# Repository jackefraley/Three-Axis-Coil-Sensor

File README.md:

# Coil Array Block Project
This folder contains a KiCad hardware design for a magnetic-field sensing block.

## Project
### CoilArrayBlock
Analog sensing block containing only:

- Current transformer front end: CWS CT-0705-HA (CT-0705-HA)
- Instrumentation amplifier stage: AD8422 (AD8422ARMZ)
- Input/output connector stage: JST B2B-XH-A (B2B-XH-A)

## Interfaces
- `Env_array_magfield`: magnetic field input to the sensing front end
- `Pwr_array_dcpwr`: `VCC` supply input
- `Pwr_array_vref`: `Vref` reference input
- `Array_sigproc_asig`: `Vout` analog signal output

## Repository Notes
This project includes KiCad source files (`.kicad_sch`, `.kicad_pcb`, `.kicad_pro`) and generated Gerbers.
Supporting documentation is included in `docs/`.
KiCad backup archives and local transient files are excluded via `.gitignore`.

## PCB Image

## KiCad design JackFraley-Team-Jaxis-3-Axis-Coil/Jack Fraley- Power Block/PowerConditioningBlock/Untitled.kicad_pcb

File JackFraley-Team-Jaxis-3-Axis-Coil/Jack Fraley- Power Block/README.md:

# Power Conditioning Block Projects

This folder contains two KiCad hardware designs split by function.

## Projects

### `PowerBlock`
Power supply block containing only:

- 5V buck converter: `LM62460Q1` (LM62460QRPHRQ1)
- 3.3V linear regulator: `TPS7A94` (PTPS7A9401DSCR)
- Comparator stage: `TLV6710` (TLV6710DDCT)

### `PowerConditioningBlock`
Precision conditioning/reference block containing:

- `ADR4525` precision voltage reference (ADR4525ARZ)
- `TPS7A94` low-noise LDO (PTPS7A9401DSCR)
- `OPA2211` precision op-amp (OPA2211AIDDAR)

## Repository Notes

- Each project includes KiCad source files (`.kicad_sch`, `.kicad_pcb`, `.kicad_pro`) and generated Gerbers.
- KiCad backup archives and local transient files are excluded via `.gitignore`.

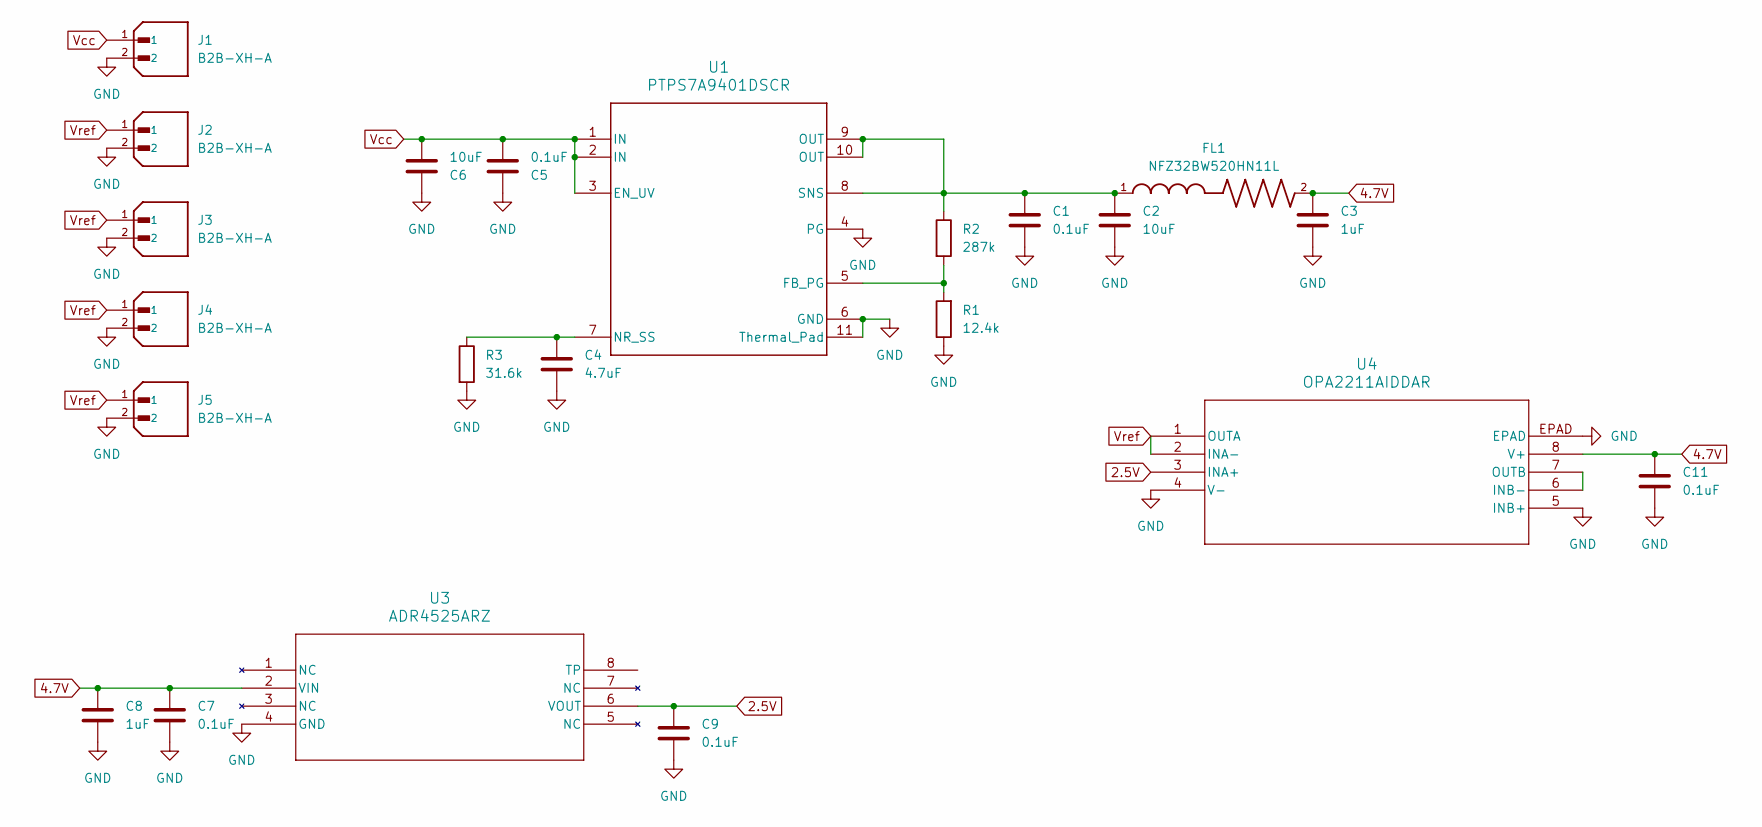
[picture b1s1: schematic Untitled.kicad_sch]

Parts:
C1, C5, C7, C9, C11: 0.1uF; C_0603_1608Metric
C2, C6: 10uF; C_0603_1608Metric
C3, C8: 1uF; C_0603_1608Metric
C4: 4.7uF; C_0603_1608Metric
FL1: NFZ32BW520HN11L; FIL_NFZ32BW520HN11L; DigiKey_Part_Number 490-NFZ32BW520HN11LCT-ND
J1, J2, J3, J4, J5: B2B-XH-A; JST_B2P-VH_LF__SN_; PARTREV N/A
R1: 12.4k; R_0603_1608Metric
R2: 287k; R_0603_1608Metric
R3: 31.6k; R_0603_1608Metric
U1: PTPS7A9401DSCR; DSC0010J-MFG
U3: ADR4525ARZ; R_8_ADI
U4: OPA2211AIDDAR; DDA8_3X2P49

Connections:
2.5V: C9.1, U3.6 (VOUT), U4.3 (INA+)
4.7V: C3.1, C7.1, C8.1, C11.1, FL1.2, U3.2 (VIN), U4.8 (V+)
GND: C1.2, C2.2, C3.2, C4.2, C5.1, C6.1, C7.2, C8.2, C9.2, C11.2, J1.2, J2.2, J3.2, J4.2, J5.2, R1.1, R3.2, U1.4 (PG), U1.6 (GND), U1.11 (Thermal_Pad), U1.12, U1.13, U1.14, U1.15, U3.4 (GND), U4.4 (V-), U4.5 (INB+), U4.EPAD
unnamed: R1.2, R2.2, U1.5 (FB_PG)
unnamed: C4.1, R3.1, U1.7 (NR_SS)
unnamed: C1.1, C2.1, FL1.1, R2.1, U1.8 (SNS), U1.9 (OUT), U1.10 (OUT)
unnamed: U4.6 (INB-), U4.7 (OUTB)
Vcc: C5.2, C6.2, J1.1, U1.1 (IN), U1.2 (IN), U1.3 (EN_UV)
Vref: J2.1, J3.1, J4.1, J5.1, U4.1 (OUTA), U4.2 (INA-)

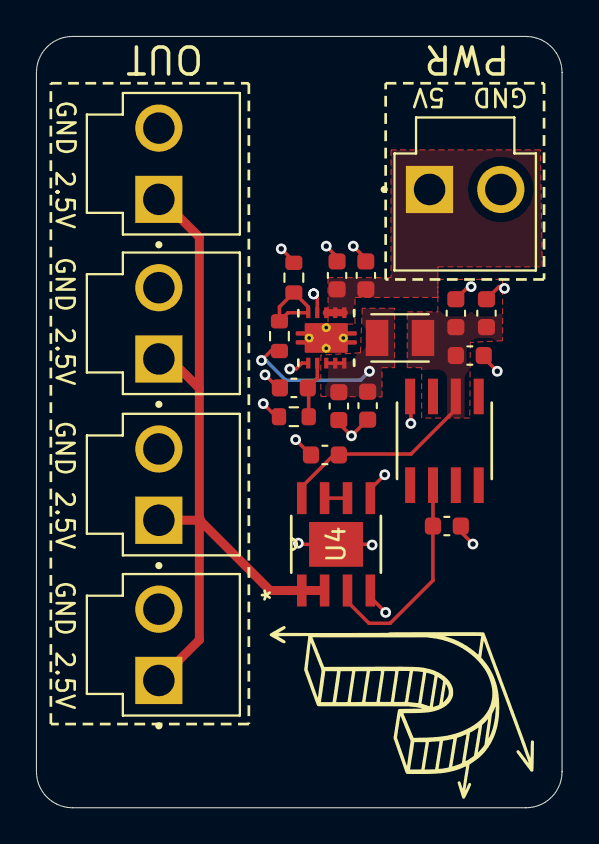
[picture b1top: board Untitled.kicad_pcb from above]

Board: 2 copper layers, 29.2 x 42.9 mm, 22 parts (0 on the bottom side), 9 nets.

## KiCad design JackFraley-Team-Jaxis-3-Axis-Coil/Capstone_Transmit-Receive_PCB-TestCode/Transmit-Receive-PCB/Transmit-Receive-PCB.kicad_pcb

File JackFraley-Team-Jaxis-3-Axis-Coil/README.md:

# Team-Jaxis-3-Axis-Coil
Documentation, resources, code, schematics, pcb layouts, and all related materials for the 3-Axis Coil ECE project at Oregon State University.

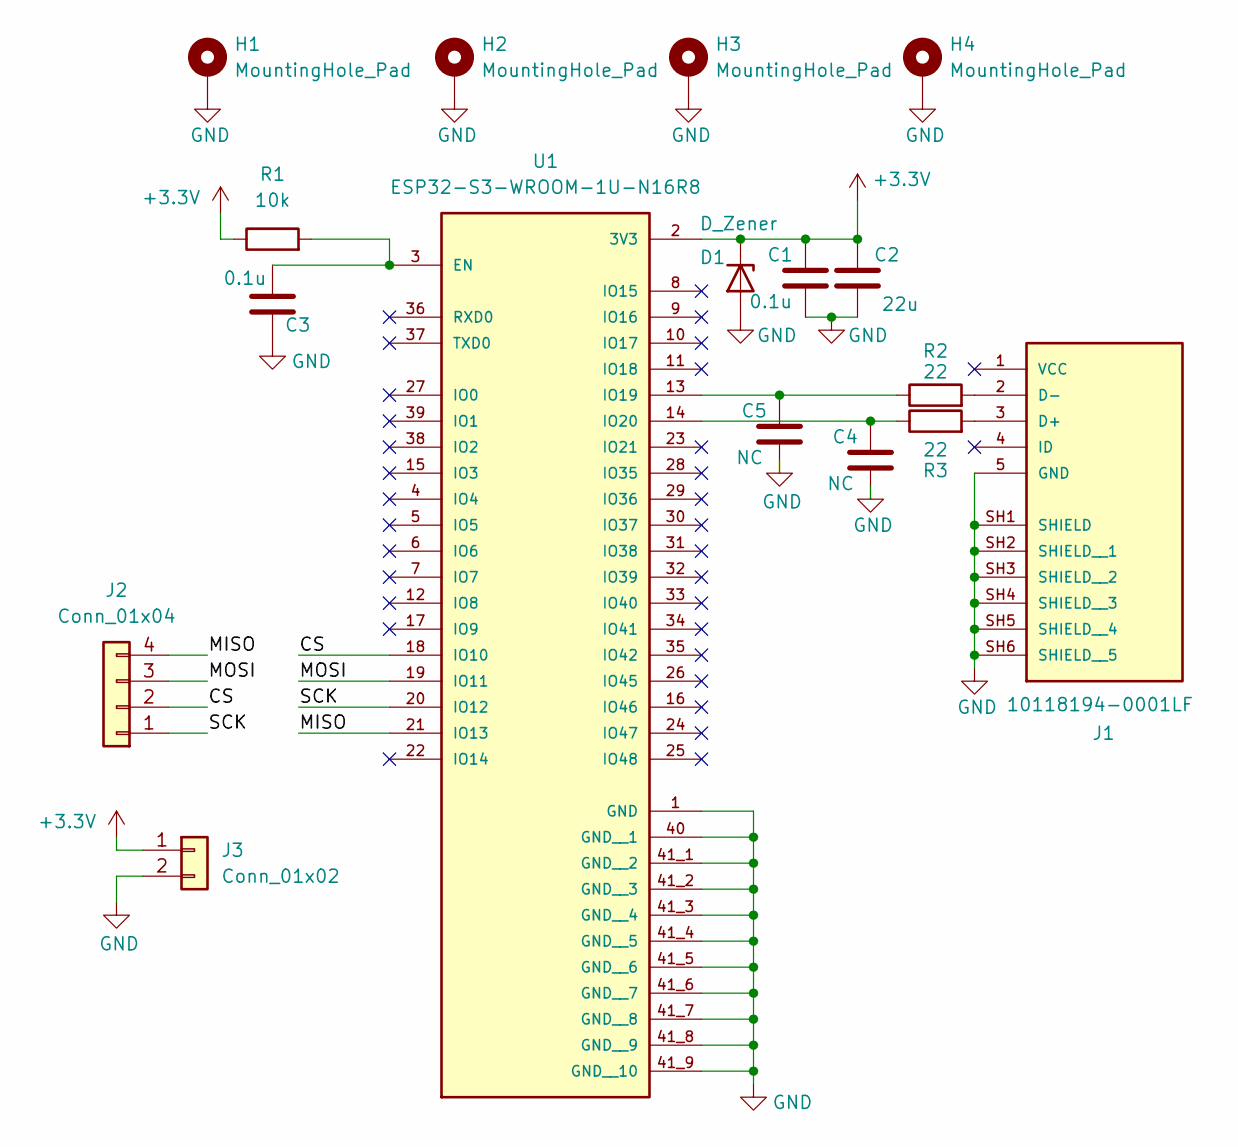
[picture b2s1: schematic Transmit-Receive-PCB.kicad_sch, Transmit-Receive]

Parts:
C1, C3: 0.1u; C_0805_2012Metric_Pad1.18x1.45mm_HandSolder
C2: 22u; C_0805_2012Metric_Pad1.18x1.45mm_HandSolder
C4, C5: NC; C_0805_2012Metric_Pad1.18x1.45mm_HandSolder
D1: D_Zener; SOD123_DIO
H1, H2, H3, H4: MountingHole_Pad; MountingHole_2.2mm_M2_Pad
J1: 10118194-0001LF; AMPHENOL_10118194-0001LF; PARTREV D
J2: Conn_01x04; JST_XH_B4B-XH-AM_1x04_P2.50mm_Vertical
J3: Conn_01x02; JST_XH_B2B-XH-AM_1x02_P2.50mm_Vertical
R1: 10k; R_0805_2012Metric_Pad1.20x1.40mm_HandSolder
R2, R3: 22; R_0805_2012Metric_Pad1.20x1.40mm_HandSolder
U1: ESP32-S3-WROOM-1U-N16R8; XCVR_ESP32-S3-WROOM-1U-N16R8; PARTREV v1.1

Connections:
+3.3V: C1.2, C2.2, D1.1 (K), J3.1, R1.1, U1.2 (3V3)
/CS: J2.2, U1.18 (IO10)
/MISO: J2.4, U1.21 (IO13)
/MOSI: J2.3, U1.19 (IO11)
/SCK: J2.1, U1.20 (IO12)
GND: C1.1, C2.1, C3.2, C4.1, C5.1, D1.2 (A), H1.1, H2.1, H3.1, H4.1, J1.5 (GND), J1.SH1 (SHIELD), J1.SH2 (SHIELD__1), J1.SH3 (SHIELD__2), J1.SH4 (SHIELD__3), J1.SH5 (SHIELD__4), J1.SH6 (SHIELD__5), J3.2, U1.1 (GND), U1.40 (GND__1), U1.41_1 (GND__2), U1.41_2 (GND__3), U1.41_3 (GND__4), U1.41_4 (GND__5), U1.41_5 (GND__6), U1.41_6 (GND__7), U1.41_7 (GND__8), U1.41_8 (GND__9), U1.41_9 (GND__10), U1.41_10, U1.41_11, U1.41_12, U1.41_13, U1.41_14, U1.41_15, U1.41_16, U1.41_17, U1.41_18, U1.41_19, U1.41_20, U1.41_21
unnamed: J1.3 (D+), R3.2
unnamed: J1.2 (D-), R2.2
unnamed: C3.1, R1.2, U1.3 (EN)
unnamed: C5.2, R2.1, U1.13 (IO19)
unnamed: C4.2, R3.1, U1.14 (IO20)

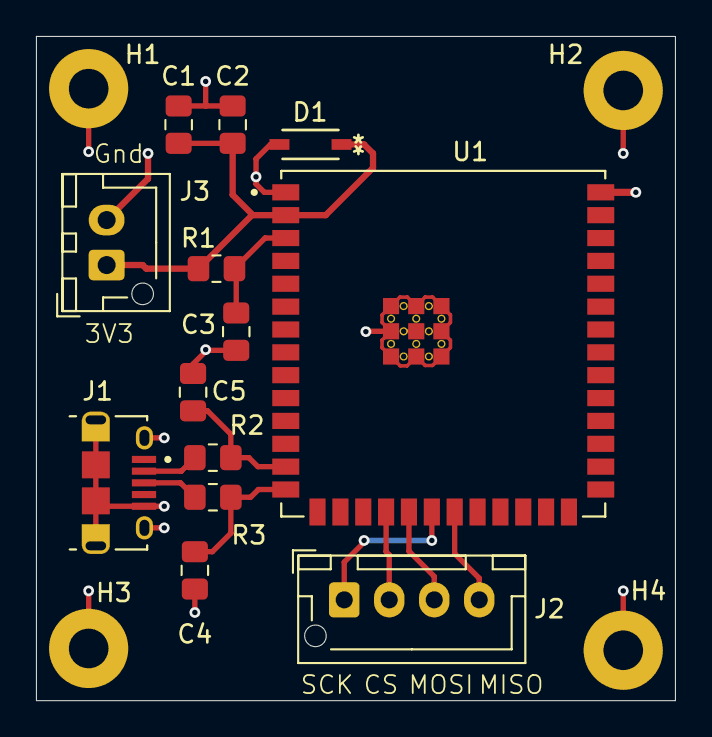
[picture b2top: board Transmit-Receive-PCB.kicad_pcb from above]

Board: 4 copper layers, 35.5 x 36.9 mm, 17 parts (0 on the bottom side), 11 nets.

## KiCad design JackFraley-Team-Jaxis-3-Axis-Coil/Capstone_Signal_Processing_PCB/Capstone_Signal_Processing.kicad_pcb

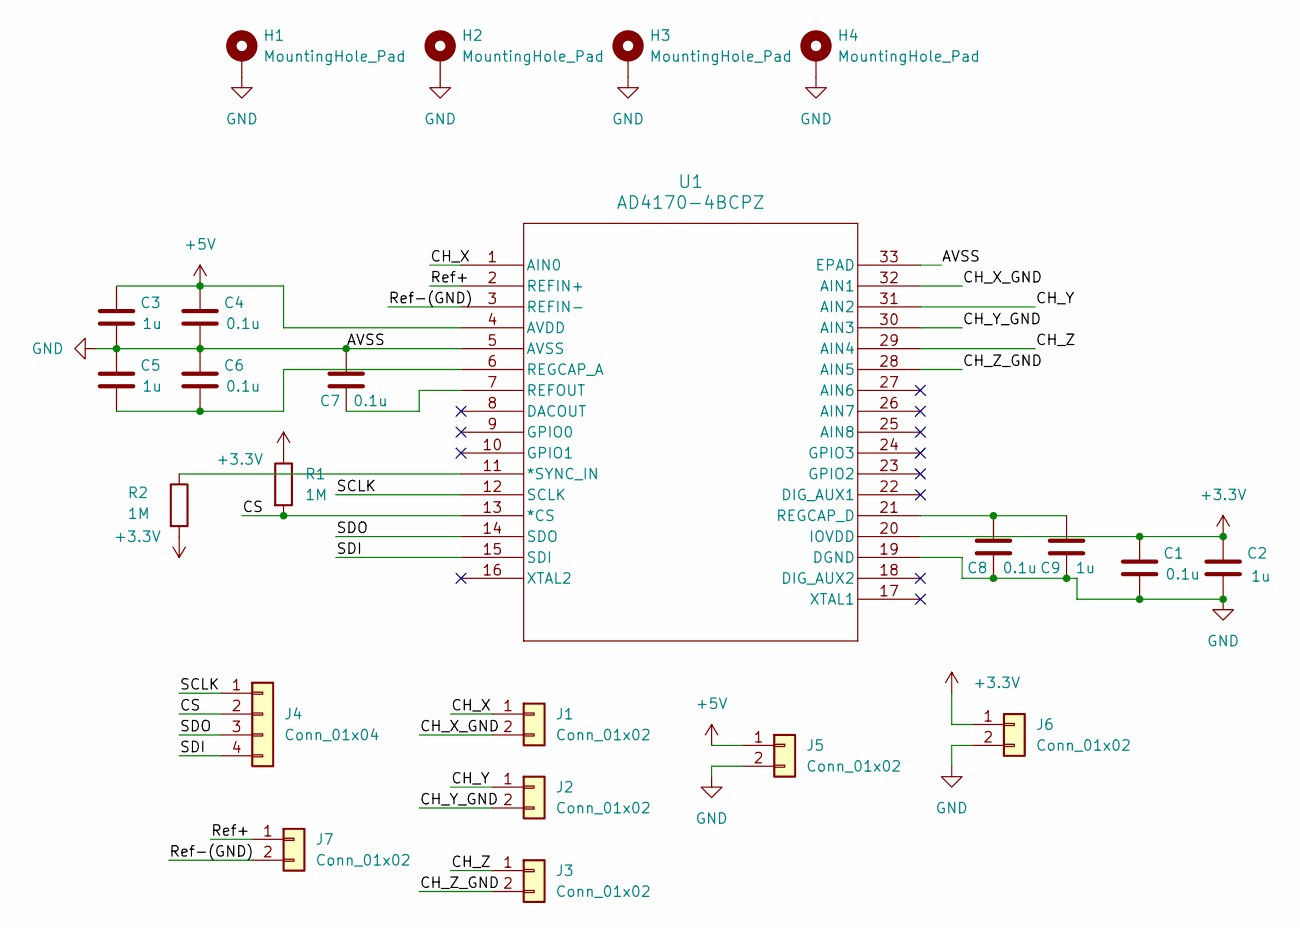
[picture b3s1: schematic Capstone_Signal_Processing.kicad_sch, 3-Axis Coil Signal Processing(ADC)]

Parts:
C1, C4, C6, C7, C8: 0.1u; C_0805_2012Metric_Pad1.18x1.45mm_HandSolder
C2, C3, C5, C9: 1u; C_0805_2012Metric_Pad1.18x1.45mm_HandSolder
H1, H2, H3, H4: MountingHole_Pad; MountingHole_2.2mm_M2_Pad
J1, J2, J3, J5, J6, J7: Conn_01x02; JST_XH_B2B-XH-AM_1x02_P2.50mm_Vertical
J4: Conn_01x04; JST_XH_B4B-XH-AM_1x04_P2.50mm_Vertical
R1, R2: 1M; R_0805_2012Metric_Pad1.20x1.40mm_HandSolder
U1: AD4170-4BCPZ; CP-32-34_ADI

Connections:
+3.3V: C1.1, C2.1, J6.1, R1.1, R2.2, U1.20 (IOVDD)
+5V: C3.1, C4.1, J5.1, U1.4 (AVDD)
/CH_X: J1.1, U1.1 (AIN0)
/CH_X_GND: J1.2, U1.32 (AIN1)
/CH_Y: J2.1, U1.31 (AIN2)
/CH_Y_GND: J2.2, U1.30 (AIN3)
/CH_Z: J3.1, U1.29 (AIN4)
/CH_Z_GND: J3.2, U1.28 (AIN5)
/CS: J4.2, R1.2, U1.13 (*CS)
/Ref+: J7.1, U1.2 (REFIN+)
/Ref-(GND): J7.2, U1.3 (REFIN-)
/SCLK: J4.1, U1.12 (SCLK)
/SDI: J4.4, U1.15 (SDI)
/SDO: J4.3, U1.14 (SDO)
GND: C1.2, C2.2, C3.2, C4.2, C5.1, C6.1, C7.1, C8.2, C9.2, H1.1, H2.1, H3.1, H4.1, J5.2, J6.2, U1.5 (AVSS), U1.19 (DGND), U1.33 (EPAD)
unnamed: R2.1, U1.11 (*SYNC_IN)
unnamed: C7.2, U1.7 (REFOUT)
unnamed: C5.2, C6.2, U1.6 (REGCAP_A)
unnamed: C8.1, C9.1, U1.21 (REGCAP_D)

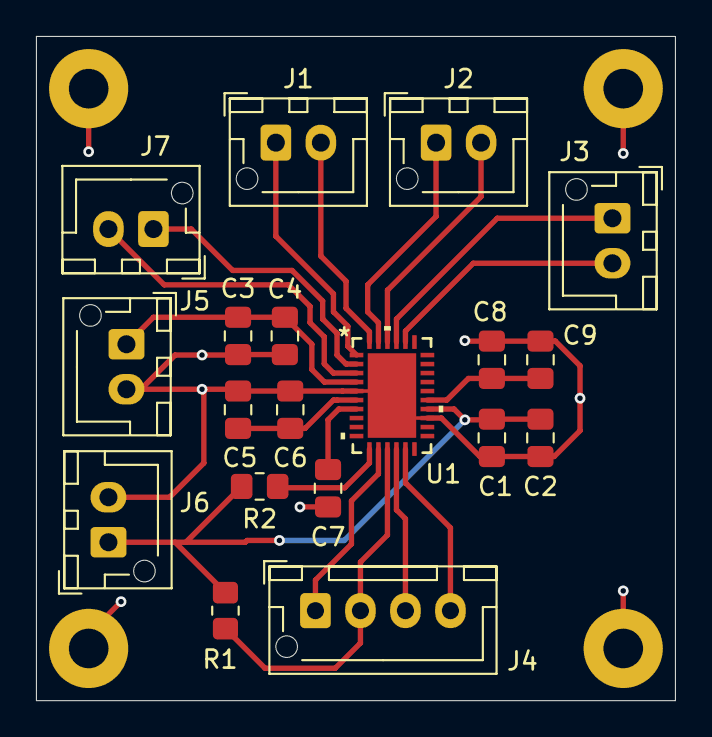
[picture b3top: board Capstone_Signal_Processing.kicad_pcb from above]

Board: 4 copper layers, 35.5 x 36.9 mm, 23 parts (0 on the bottom side), 19 nets.

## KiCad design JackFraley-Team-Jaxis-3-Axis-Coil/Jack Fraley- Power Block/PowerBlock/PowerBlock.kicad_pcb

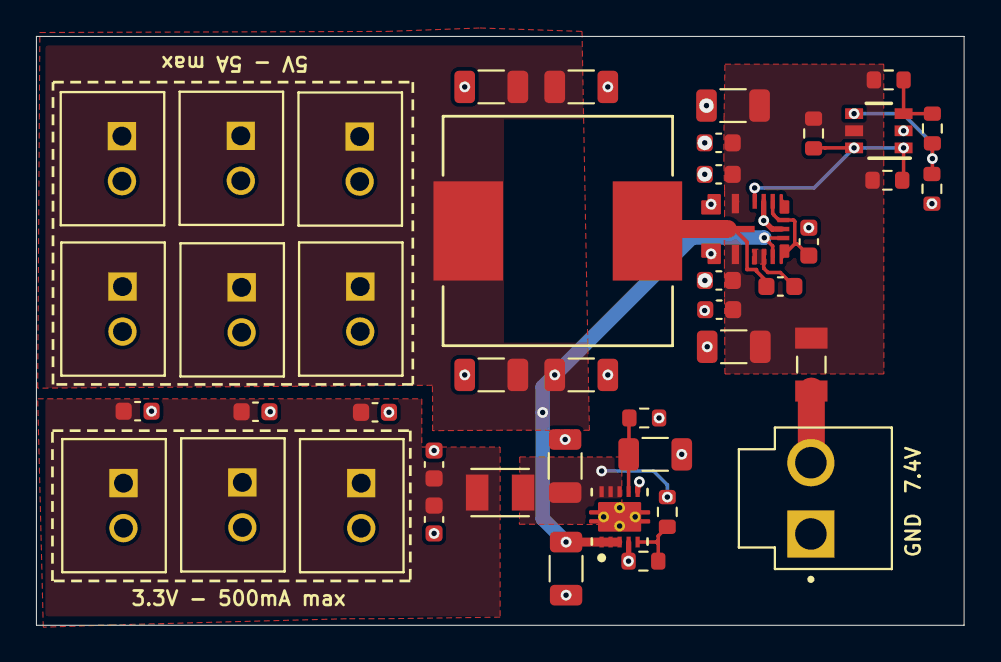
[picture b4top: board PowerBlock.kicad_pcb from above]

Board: 2 copper layers, 51.5 x 32.7 mm, 44 parts (0 on the bottom side), 14 nets.

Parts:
C1: 1uF; C_0603_1608Metric
C2, C3, C4, C5: 0.1uF; C_0603_1608Metric
CBOOT1: 0.1uF; C_0603_1608Metric
CHF1A1, CHF1B1, CHF2A1, CHF2B1: 0.47uF; C_0603_1608Metric
CIN1, CIN2, CIN4: 10uF; C_1206_3216Metric
CNRSS1: 4.7uF; C_1206_3216Metric
COUT4: 10uF; C_1206_3216Metric
COUT51, COUT52, COUT53, COUT54: 22uF; C_1206_3216Metric
CVCC1: 1uF; C_0603_1608Metric
F1: 0685T7000-01; FUSC3215X83N
FL1: NFZ32BW520HN11L; FIL_NFZ32BW520HN11L
J1: B2P-VH_LF__SN_; JST_B2P-VH_LF__SN_
J2, J3, J4, J5, J6, J7, J8, J9, J10: B2B-XH-A; JST_B2B-XH-A
L1: 4.7uH; DR125
R1: 649k; R_0603_1608Metric
R2: 12.8k; R_0603_1608Metric
R3: 31.1k; R_0603_1608Metric
R4, R5: 100k; R_0603_1608Metric
RFB_PGB1: 100k; R_0603_1608Metric
RFB_PGT1: 1.47M; R_0603_1608Metric
RNRSS1: 22.1k; R_0603_1608Metric
U1: LM62460QRPHRQ1; RPH0016A
U2: TLV6710DDCT; DDC0006A_N
U5: PTPS7A9401DSCR; DSC0010J-MFG

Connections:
GND: C1.2, C2.1, C3.1, C4.2, C5.2, CHF1A1.2, CHF1B1.2, CHF2A1.1, CHF2B1.1, CIN1.1, CIN2.1, CIN4.2, CNRSS1.2, COUT4.2, COUT51.2, COUT52.2, COUT53.2, COUT54.2, CVCC1.2, J1.1, J2.2, J3.2, J4.2, J5.2, J6.2, J7.2, J8.2, J9.2, J10.2, R3.1, RFB_PGB1.1, RNRSS1.2, U1.1 (PGND), U1.8 (AGND), U1.12 (SYNC_MODE), U1.15 (PGND), U2.2 (GND), U5.4 (PG), U5.6 (GND), U5.11 (Thermal_Pad)
unnamed: C1.1, C2.2, C3.2, C4.1, C5.1, FL1.2, J2.1, J3.1, J4.1
unnamed: F1.1, J1.2
unnamed: CIN4.1, COUT51.1, COUT52.1, COUT53.1, COUT54.1, J5.1, J6.1, J7.1, J8.1, J9.1, J10.1, L1.2, U1.5 (BIAS), U1.7 (FB), U5.1 (IN), U5.2 (IN), U5.3 (EN_UV)
unnamed: CBOOT1.2, U1.3 (RBOOT), U1.4 (CBOOT)
unnamed: R4.2, R5.1, U1.13 (EN), U2.1 (OUTA), U2.6 (OUTB)
unnamed: CVCC1.1, U1.6 (VCC), U1.9 (RT), U1.11 (SpSp)
unnamed: CBOOT1.1, L1.1, U1.16 (SW)
unnamed: R1.1, R2.1, U2.3 (INA+)
unnamed: R2.2, R3.2, U2.4 (INB-)
unnamed: CHF1A1.1, CHF1B1.1, CHF2A1.2, CHF2B1.2, CIN1.2, CIN2.2, F1.2, R1.2, R4.1, R5.2, U1.2 (VIN), U1.14 (VIN), U2.5 (VDD)
unnamed: RFB_PGB1.2, RFB_PGT1.2, U5.5 (FB_PG)
unnamed: CNRSS1.1, RNRSS1.1, U5.7 (NR_SS)
unnamed: COUT4.1, FL1.1, RFB_PGT1.1, U5.8 (SNS), U5.9 (OUT), U5.10 (OUT)

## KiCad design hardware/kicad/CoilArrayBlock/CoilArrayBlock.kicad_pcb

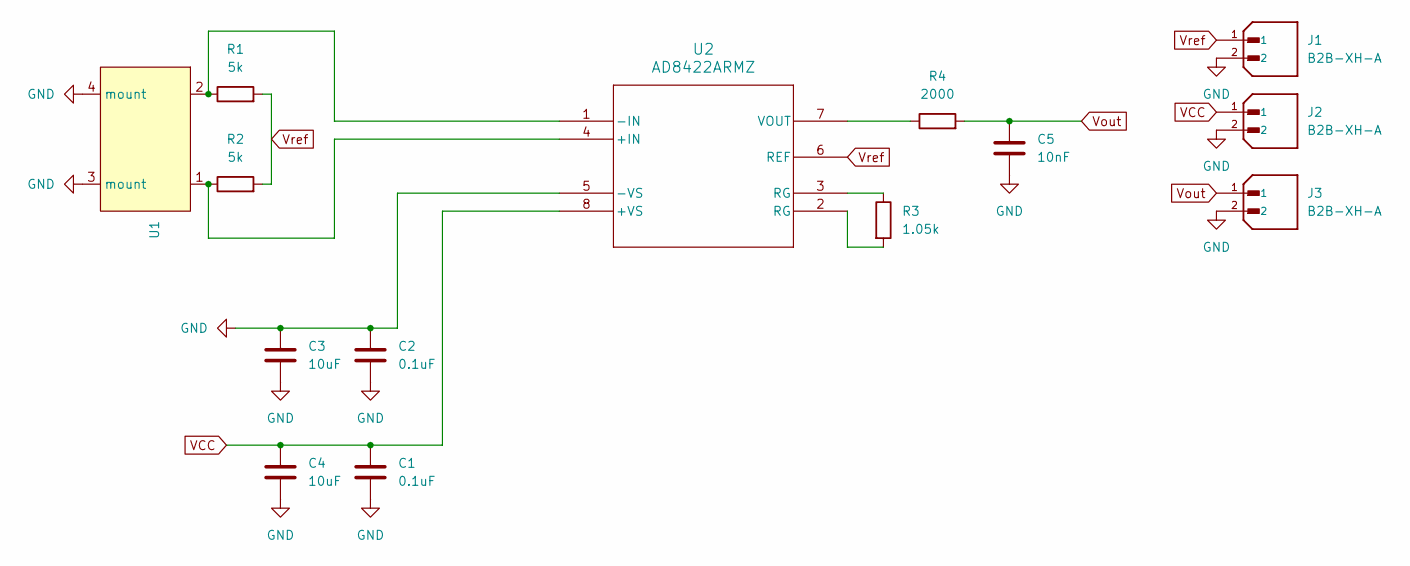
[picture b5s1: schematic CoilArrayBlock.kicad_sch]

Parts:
C1, C2: 0.1uF; C_0603_1608Metric
C3, C4: 10uF; C_0603_1608Metric
C5: 10nF; C_0603_1608Metric
J1, J2, J3: B2B-XH-A; JST_B2B-XH-A; PARTREV N/A
R1, R2: 5k; C_0603_1608Metric
R3: 1.05k; C_0603_1608Metric
R4: 2000; C_0603_1608Metric
U1: CT-0705-HA
U2: AD8422ARMZ; RM_8_ADI

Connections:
GND: C1.1, C2.1, C2.2, C3.1, C3.2, C4.2, C5.2, J1.2, J2.2, J3.2, U1.3 (mount), U1.4 (mount), U2.5 (-VS)
unnamed: R3.1, U2.3 (RG)
unnamed: R3.2, U2.2 (RG)
unnamed: R2.1, U1.1, U2.4 (+IN)
unnamed: R1.1, U1.2, U2.1 (-IN)
unnamed: R4.1, U2.7 (VOUT)
VCC: C1.2, C4.1, J2.1, U2.8 (+VS)
Vout: C5.1, J3.1, R4.2
Vref: J1.1, R1.2, R2.2, U2.6 (REF)

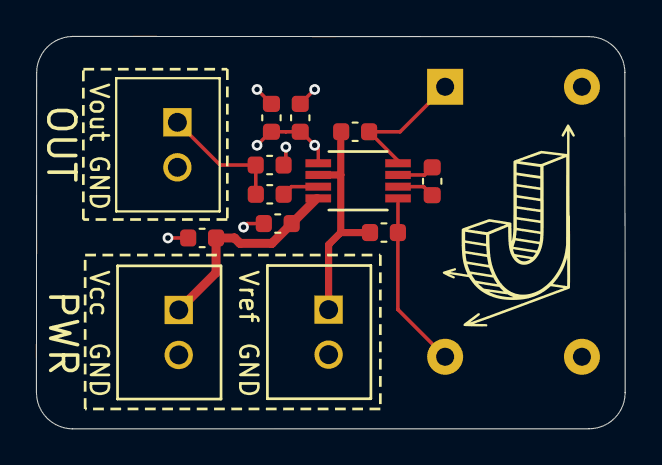
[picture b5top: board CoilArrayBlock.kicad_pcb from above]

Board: 2 copper layers, 32.7 x 21.8 mm, 14 parts (1 on the bottom side), 9 nets.

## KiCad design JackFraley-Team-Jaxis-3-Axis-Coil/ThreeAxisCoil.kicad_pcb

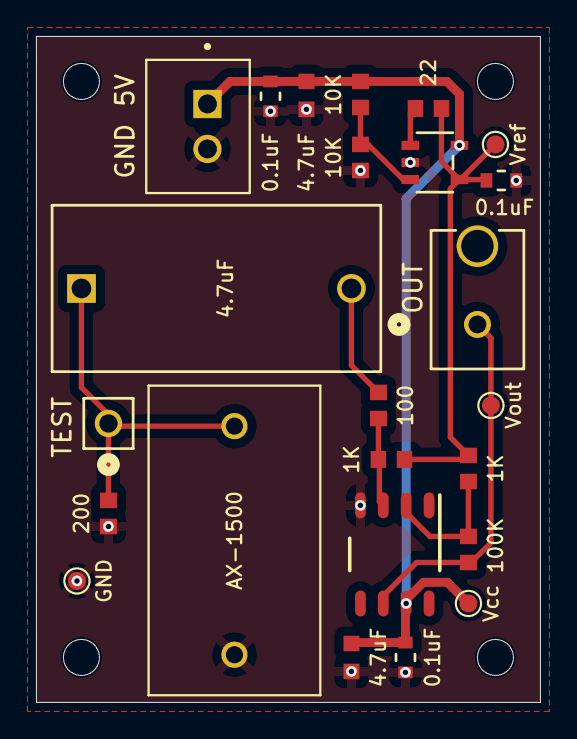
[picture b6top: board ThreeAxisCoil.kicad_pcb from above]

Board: 2 copper layers, 28.0 x 37.0 mm, 24 parts (0 on the bottom side), 10 nets.

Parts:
C1: 4.7uF; CAP_B32522_09.0X17.5X18.0_TDK
C2, C4, C6: 0.1uF; CAP_CL10_SAM
C3, C5: 4.7uF; CAP_0603_CL10A_1P6XP8_SAM
GND: TestPoint_Pad_D1.0mm
J1: B2B-XH-A; JST_B2B-XH-A
J2: B1B-XH-AMLFSNP; CONN_B1B-XH-AMLFSNP_JST
J3: PH1-01-UA; CONN_PH1-01-UA_ADM
R1: 200; RES_TNPW0603_VIS
R2, R3: 10K; RES_TNPW0603_VIS
R4, R6: 1K; RES_TNPW0603_VIS
R5: 100; RES_TNPW0603_VIS
R7: 100K; RES_TNPW0603_VIS
R8: 22; RES_TNPW0603_VIS
T1: AX-1500; INDRR1270W55L1720T953H2040
U1: OPA1611AIDR; D0008A_N
U2: OPA187IDBVT; DBV5_TEX
Vcc: TestPoint_Pad_D1.0mm
Vout: TestPoint_Pad_D1.0mm
Vref: TestPoint_Pad_D1.0mm

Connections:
GND: C2.2, C3.2, C4.2, C5.2, C6.2, GND.1, J1.2, R1.1, R3.1, T1.3, U1.4 (V-), U2.2 (V-)
In-: R6.1, R7.2, U1.2 (IN-)
unnamed: C1.1, J3.1, R1.2, T1.1
unnamed: C1.2, R5.1
unnamed: R4.2, R5.2, U1.3 (IN+)
unnamed: J2.1, R7.1, U1.6 (OUT), Vout.1
unnamed: R8.2, U2.1 (OUT)
V2.5: R2.1, R3.2, U2.3 ('+IN)
VCC: C2.1, C3.1, C4.1, C5.1, J1.1, R2.2, U1.7 (V+), U2.5 (V+), Vcc.1
Vref: C6.1, R4.1, R6.2, R8.1, U2.4 ('-IN), Vref.1

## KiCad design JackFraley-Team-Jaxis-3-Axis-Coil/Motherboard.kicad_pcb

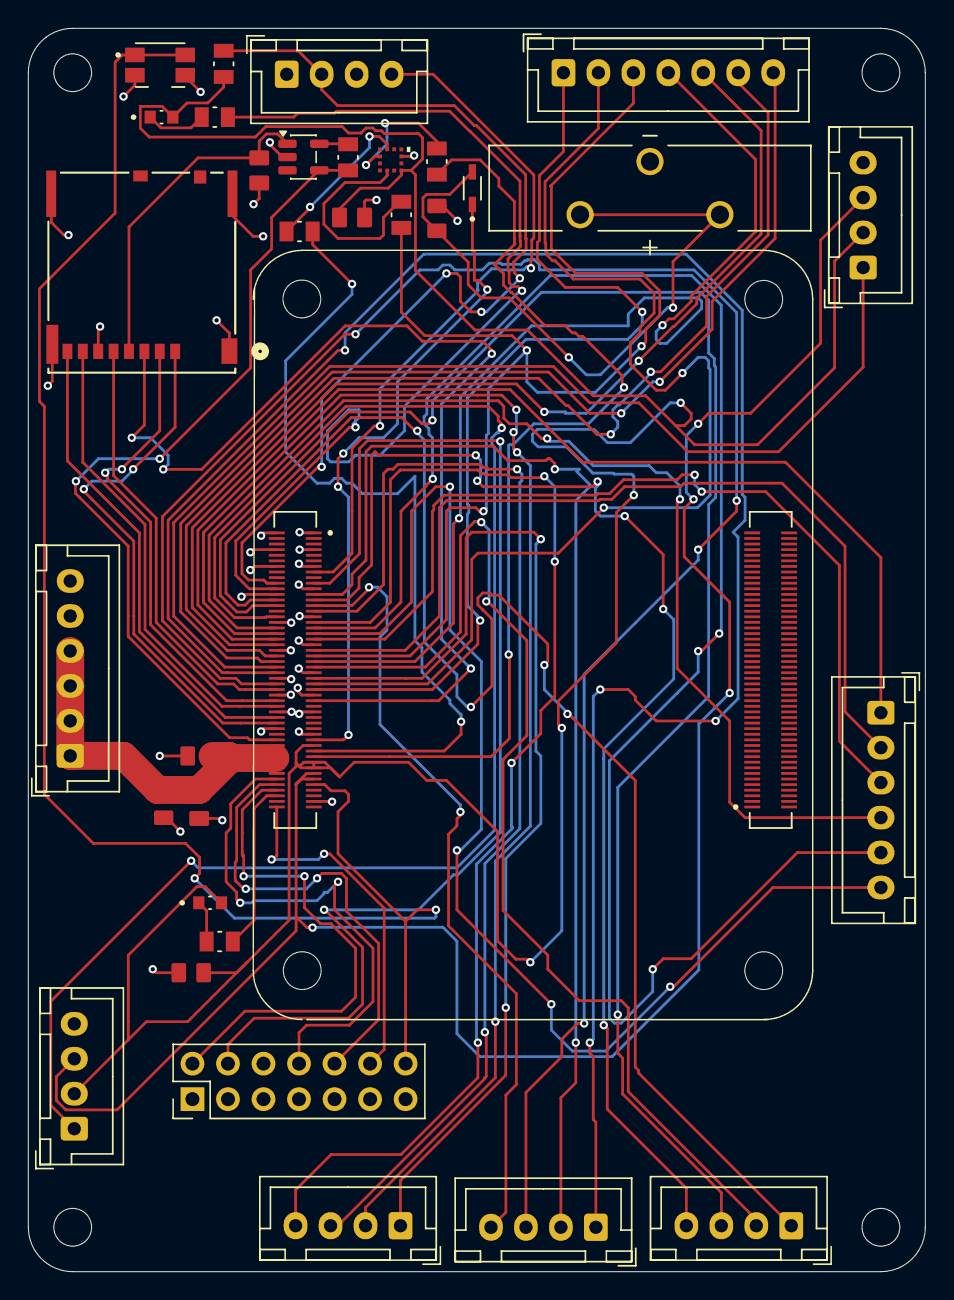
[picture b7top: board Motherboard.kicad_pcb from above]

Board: 2 copper layers, 64.1 x 88.9 mm, 42 parts (0 on the bottom side), 59 nets.

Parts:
BT1: 1074; BAT_1074
C1: 10u; CAPC2012X140N
C2: 4.7u; CAPC2012X140N
C3: 1uF; CAPC2012X135N
C6, C12, C13: 0.1uF; CAPC2012X95N
C7: 10uF; CAPC2012X140N
D2: ZMV829BTA; SOD2512X116N
D4, D5: LTST-C190KRKT; LEDC1608X35N
H1, H2, H3, H4, H5, H6, H7, H8: MountingHole; MountingHole_2.7mm_M2.5
J1, J8: Conn_01x06_Socket; JST_XH_B6B-XH-A_1x06_P2.50mm_Vertical
J2, J3, J4, J5, J6, J10: Conn_01x04_Socket; JST_XH_B4B-XH-A_1x04_P2.50mm_Vertical
J7: Conn_01x07_Socket; JST_XH_B7B-XH-A_1x07_P2.50mm_Vertical
J9: Conn_02x07_Odd_Even; PinHeader_2x07_P2.54mm_Vertical
J12, J13: 10164227-1001A1RLF; AMPHENOL_10164227-1001A1RLF
J14: 5033981892; CONN_503398-1892_MOL
R1, R5: 10k; RESC2012X65N
R2, R6, R7: 2.7k; RESC2012X65N
R3, R4: 1k; RESC2012X65N
S1: EVQ-P7A01P; SW_EVQ-P7A01P
U1: RT9742GGJ5; SOT-23-5
U2: MXC6655XA; MXC6655XA_MEM

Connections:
1.8VO: J5.3, J6.3, J12.87, J12.89
3.3VI: R5.1, U1.5 (IN)
3.3VO: C2.1, C13.2, D4.A, D5.A, J5.2, J6.2, J12.77, J12.83, J12.85, R1.2, U2.7 (VDD)
5VI: C6.1, C7.1, C12.1, J8.1, J8.2, J8.3, J8.4, J12.78, J12.80, J12.82, J12.84, J12.86, J12.88
BT_nDisable: J9.10, J12.92
EEPROM_nWP: J9.4, J12.19
FANPWM: J10.2, J12.20, R1.1
GND: BT1.N, C1.2, C2.2, C3.2, C6.2, C7.2, C12.2, C13.1, J5.4, J6.4, J8.5, J8.6, J9.1, J9.3, J9.5, J9.7, J9.9, J9.11, J9.13, J10.3, J12.1, J12.2, J12.7, J12.8, J12.13, J12.14, J12.21, J12.24, J12.31, J12.34, J12.41, J12.44, J12.51, J12.54, J12.59, J12.60, J12.65, J12.66, J12.72, J12.73, J12.97, J14.6 (VSS), J14.11, J14.12, J14.13, J14.14, S1.2_1, S1.2_2, U1.2 (GND), U2.9 (GND)
GPIO0: J1.5, J12.35
GPIO1: J1.4, J12.36
GPIO2: J7.1, J12.57
GPIO3: J7.2, J12.55
GPIO4: J3.1, J12.53
GPIO5: J3.4, J12.33
GPIO6: J3.3, J12.29
GPIO7: J3.2, J12.38
GPIO8: J1.1, J12.40
GPIO9: J1.3, J12.39
GPIO10: J1.2, J12.43
GPIO11: J1.6, J12.37
GPIO12: J6.1, J12.32
GPIO13: J4.4, J12.27
GPIO14: J4.3, J12.56
GPIO15: J4.1, J12.52
GPIO17: J2.2, J12.49
GPIO18: J5.1, J12.50
GPIO19: J2.4, J12.25
GPIO20: J2.3, J12.28
GPIO21: J2.1, J12.26
GPIO22: J7.3, J12.45, R7.1
GPIO23: J7.7, J12.48
GPIO24: J7.6, J12.46
GPIO25: J7.5, J12.42
GPIO26: J4.2, J12.23
GPIO27: J7.4, J12.47
LED_nACT: J12.22, R3.2
unnamed: BT1.P_1, BT1.P_2, C3.1, D2.A
unnamed: D4.C, R3.1
unnamed: D5.C, R4.1
unnamed: R7.2, U2.5 (INT)
unnamed: R2.1, U2.12 (SCL)
unnamed: R6.2, U2.2 (SDA)
PMIC_ENABLE: J9.12, J12.100
PWR_BUT: J9.14, J12.91, S1.1_1, S1.1_2
SCL0: J12.79, R2.2
SDA0: J12.81, R6.1
SD_CLK: J12.58, J14.5 (CLK)
SD_CMD: J12.61, J14.3 (CMD)
SD_DAT0: J12.64, J14.7 (DA0)
SD_DAT1: J12.68, J14.8 (DAT1)
SD_DAT2: J12.70, J14.1 (DAT2)
SD_DAT3: J12.62, J14.2 (CD/DAT3)
SD_PWR: C1.1, J14.4 (VDD), U1.1 (OUT)
SD_PWR_ON: J12.76, R5.2, U1.4 (EN)
TACHO: J10.4, J12.15
VBAT: D2.K, J12.75
Wifi_nDisable: J9.8, J12.90
nPWR_LED: J12.96, R4.2
nRPIBOOT: J9.2, J12.94

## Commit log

2026-04-01 Add coil array KiCad project and revised interface validation
2026-04-01 Simplify docs and remove validation
2026-04-01 Remove scripts folder
2026-04-01 Import Team-Jaxis-3-Axis-Coil into JackFraley subfolder
2026-04-01 Remove imported Team-Jaxis subfolder
2026-04-01 Update README to power conditioning block format
2026-04-01 Rework README format for CoilArrayBlock
2026-04-01 Refine main components list format in README
2026-04-01 upload pcb image
2026-04-01 Rename image.png to CoilArrayPCB.png
2026-04-01 Add PCB image to README
2026-04-01 Move PCB image section to bottom of README
